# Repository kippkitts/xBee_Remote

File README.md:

xBee_Remote
===========

The XBee Remote is a fully programmable remote control that can be used to operate robots or other systems that are equipped with an XBee transceiver.  It features two thumb joysticks, five pushbutton switches, and an LCD display, the functions of which can be programmed into the onboard Atmega32u4 microcontroller.  This repository contains the Eagle files for the remote.

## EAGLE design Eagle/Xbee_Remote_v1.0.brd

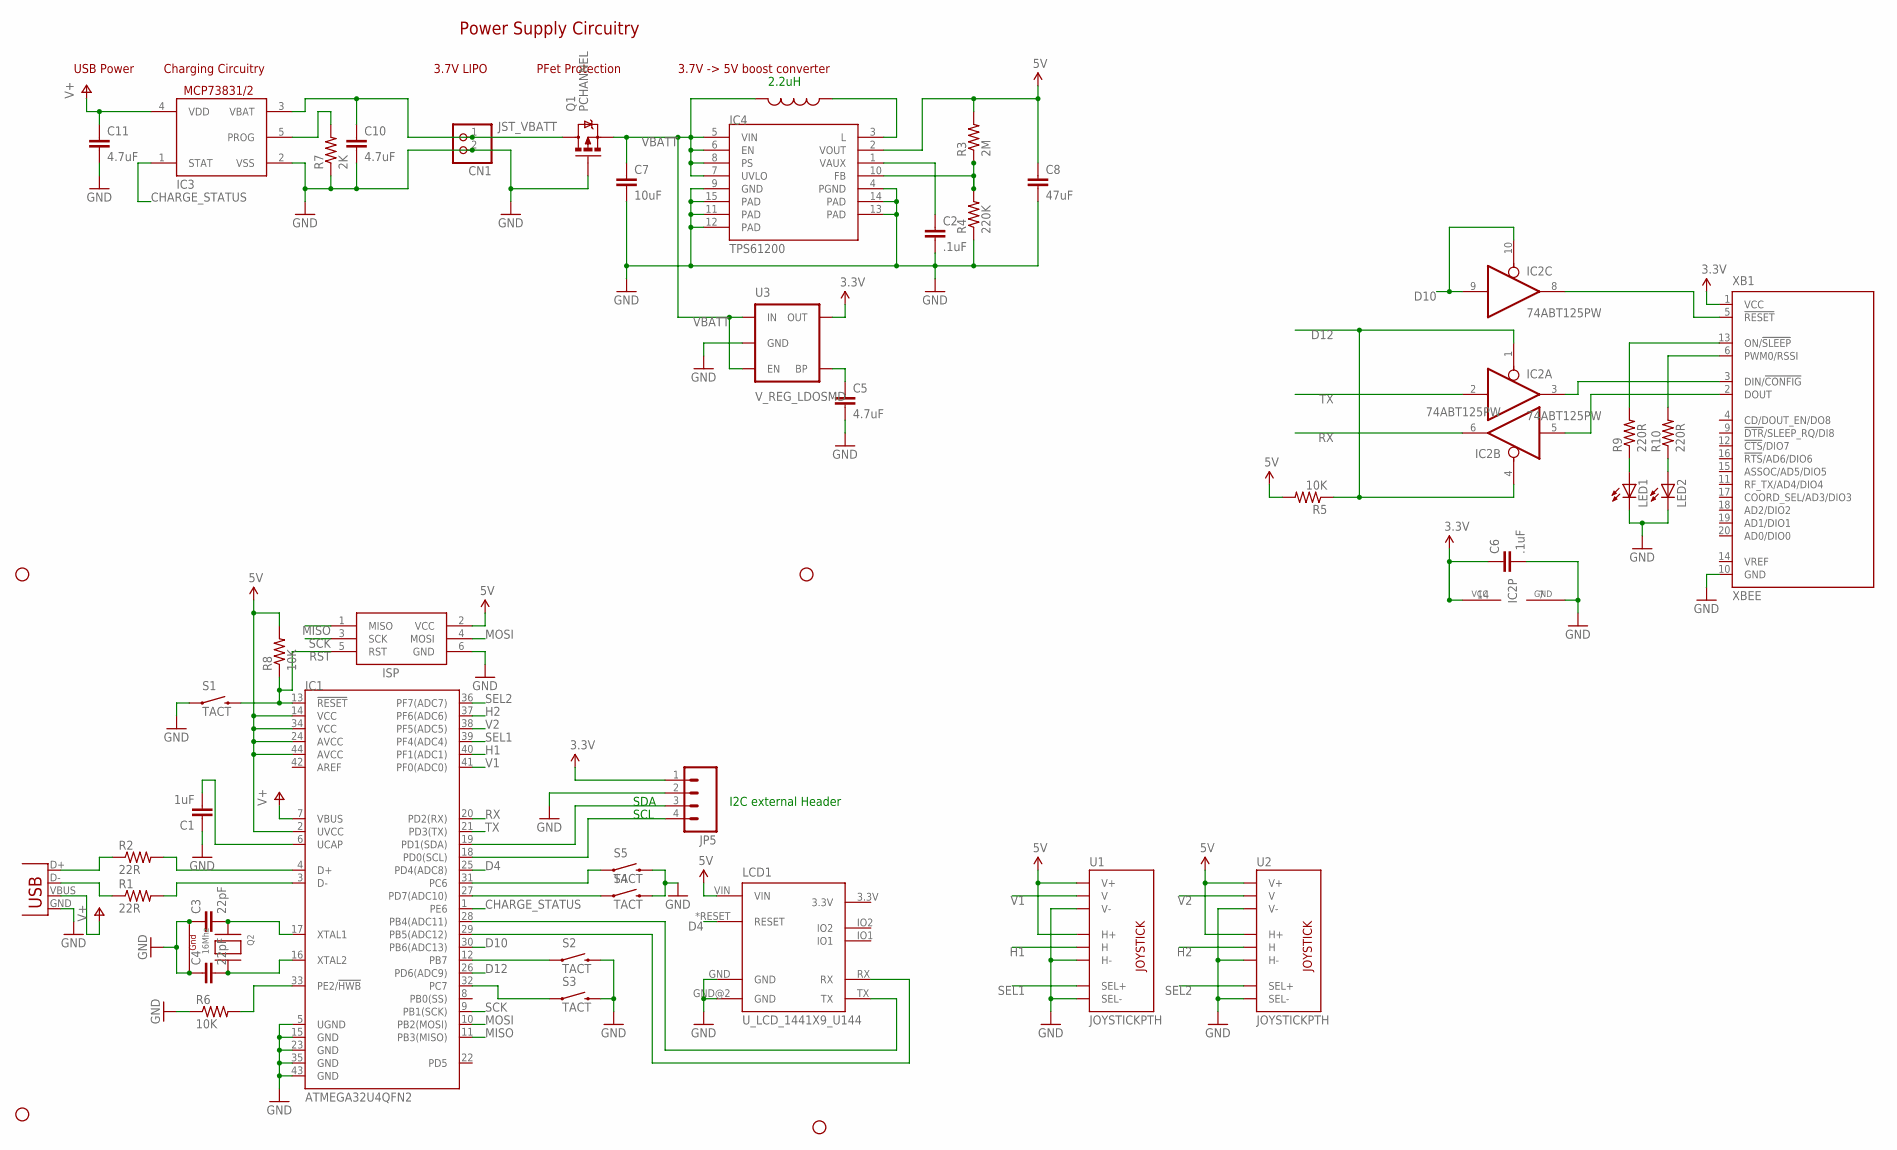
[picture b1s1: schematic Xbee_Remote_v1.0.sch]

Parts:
C1: 1uF; 0805
C2, C6: .1uF; 0805
C3, C4: 22pF; 0805
C5, C10, C11: 4.7uF; 0805
C7: 10uF; 0805
C8: 47uF; 1206
CN1: JST_2PIN-SMT-RA; JST-PH-2-SMT-RA
IC1: ATMEGA32U4QFN2; QFN-44-NOPAD
IC2: 74ABT125PW; TSSOP14
IC3: MCP73831/OT; SOT23-5L
IC4: TPS61200; QFN-10_PAD
ISP: AVRISP-6; AVRISP
JP1, JP2, JP3, JP4: STAND-OFF
JP5: M04PTH; 1X04
L1: 2.2uH; COILCRAFT_EPL2014
LCD1: U_LCD_1441X9_U144; U_LCD_144
LED1, LED2: LEDCHIPLED_0805; CHIPLED_0805
Q1: PCHANNEL; SOT23-3
Q2: 16Mhz; NX3225
R1, R2: 22R; 0805
R3: 2M; 0805
R4: 220K; 0805
R5, R6, R8: 10K; 0805
R7: 2K; 0805
R9, R10: 220R; 0805
S1, S2, S3, S4, S5: TACT; TACTILE_SWITCH_SMD
U1, U2: JOYSTICKPTH; JOYSTICK
U3: V_REG_LDOSMD; SOT23-5
X1: USB-MICROB
XB1: XBEE

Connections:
3.3V: C6.1, IC2.14 (VCC), JP5.1, U3.5 (OUT), XB1.1 (VCC)
5V: C8.1, IC1.2 (UVCC), IC1.14 (VCC), IC1.24 (AVCC), IC1.34 (VCC), IC1.44 (AVCC), IC4.2 (VOUT), ISP.2 (VCC), LCD1.VIN, R3.2, R5.2, R8.2, U1.H1 (H+), U1.V1 (V+), U2.H1 (H+), U2.V1 (V+)
CHARGE_STATUS: IC1.1 (PE6), IC3.1 (STAT)
D2: IC1.19 (PD1(SDA)), JP5.3
D3: IC1.18 (PD0(SCL)), JP5.4
D4: IC1.25 (PD4(ADC8)), LCD1.*RESET (RESET)
D5: IC1.31 (PC6), S5.1
D6: IC1.27 (PD7(ADC10)), S4.1
D10: IC1.30 (PB6(ADC13)), IC2.9 (I), IC2.10 (OE)
D11: IC1.12 (PB7), S2.1
D12: IC1.26 (PD6(ADC9)), IC2.1 (OE), IC2.4 (OE), R5.1
D13: IC1.32 (PC7), S3.1
GND: C1.1, C2.2, C3.1, C4.1, C5.2, C6.2, C7.2, C8.2, C10.2, C11.2, CN1.2 (1), IC1.5 (UGND), IC1.15 (GND), IC1.23 (GND), IC1.35 (GND), IC1.43 (GND), IC2.7 (GND), IC3.2 (VSS), IC4.4 (PGND), IC4.9 (GND), IC4.11 (PAD), IC4.12 (PAD), IC4.13 (PAD), IC4.14 (PAD), IC4.15 (PAD), ISP.6 (GND), JP5.2, LCD1.GND, LCD1.GND@2 (GND), LED1.C, LED2.C, Q1.1 (G), Q2.2 (G1), Q2.4 (G2), R4.1, R6.1, R7.1, S1.1, S2.3 (2), S3.3 (2), S4.3 (2), S5.3 (2), U1.B2A (SEL-), U1.H3 (H-), U1.V3 (V-), U2.B2A (SEL-), U2.H3 (H-), U2.V3 (V-), U3.2 (GND), X1.GND, XB1.10 (GND)
H1: IC1.40 (PF1(ADC1)), U1.H2 (H)
H2: IC1.37 (PF6(ADC6)), U2.H2 (H)
JST_VBATT: C10.1, CN1.1 (2), IC3.3 (VBAT), Q1.3 (D)
LCD_RX: IC1.29 (PB5(ADC12)), LCD1.RX
LCD_TX: IC1.28 (PB4(ADC11)), LCD1.TX
MISO: IC1.11 (PB3(MISO)), ISP.1 (MISO)
MOSI: IC1.10 (PB2(MOSI)), ISP.4 (MOSI)
unnamed: R2.1, X1.D+
unnamed: R1.1, X1.D-
unnamed: IC1.4 (D+), R2.2
unnamed: IC1.3 (D-), R1.2
unnamed: C1.2, IC1.6 (UCAP)
unnamed: IC3.5 (PROG), R7.2
unnamed: IC4.3 (L), L1.P$1 (1)
unnamed: C5.1, U3.4 (BP)
unnamed: IC4.10 (FB), R3.1, R4.2
unnamed: C2.1, IC4.1 (VAUX)
unnamed: C3.2, IC1.17 (XTAL1), Q2.1 (X1)
unnamed: C4.2, IC1.16 (XTAL2), Q2.3 (X2)
unnamed: IC2.8 (O), XB1.5 (!RESET)
unnamed: IC1.33 (PE2/!HWB), R6.2
unnamed: LED1.A, R9.1
unnamed: LED2.A, R10.1
ON: R9.2, XB1.13 (ON/!SLEEP)
RSSI: R10.2, XB1.6 (PWM0/RSSI)
RST: IC1.13 (!RESET), ISP.5 (RST), R8.1, S1.3 (2)
RX: IC1.20 (PD2(RX)), IC2.6 (O)
SCK: IC1.9 (PB1(SCK)), ISP.3 (SCK)
SEL1: IC1.39 (PF4(ADC4)), U1.B1A (SEL+)
SEL2: IC1.36 (PF7(ADC7)), U2.B1A (SEL+)
TX: IC1.21 (PD3(TX)), IC2.2 (I)
V1: IC1.41 (PF0(ADC0)), U1.V2 (V)
V2: IC1.38 (PF5(ADC5)), U2.V2 (V)
V+: C11.1, IC1.7 (VBUS), IC3.4 (VDD), X1.VBUS
VBATT: C7.1, IC4.5 (VIN), IC4.6 (EN), IC4.7 (UVLO), IC4.8 (PS), L1.P$2 (2), Q1.2 (S), U3.1 (IN), U3.3 (EN)
XBEE_RX: IC2.3 (O), XB1.3 (DIN/!CONFIG)
XBEE_TX: IC2.5 (I), XB1.2 (DOUT)

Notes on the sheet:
3.7V LIPO
PFet Protection
3.7V -> 5V boost converter
Power Supply Circuitry
USB Power
Charging Circuitry
2.2uH
I2C external Header
SDA
SCL

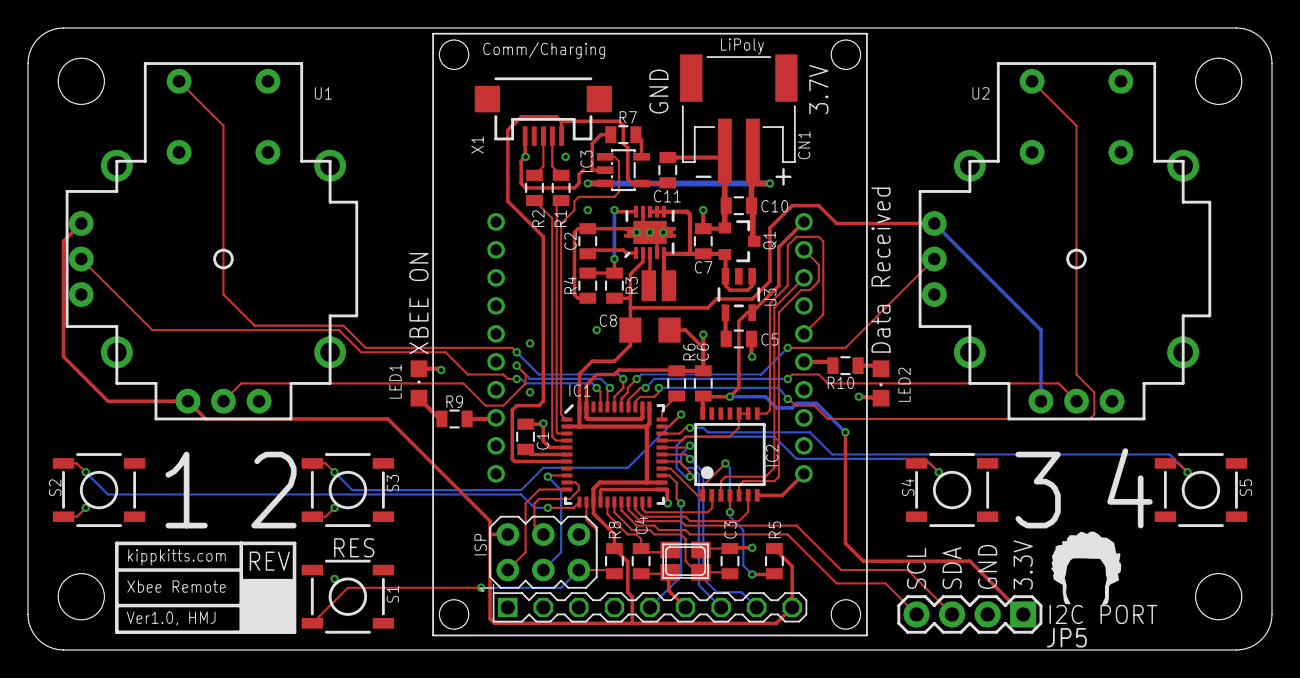
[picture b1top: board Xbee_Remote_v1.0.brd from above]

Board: 2 copper layers, 88.9 x 44.5 mm, 48 parts (1 on the bottom side), 50 nets.

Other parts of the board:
U$9: TOP_DOCU_5MM

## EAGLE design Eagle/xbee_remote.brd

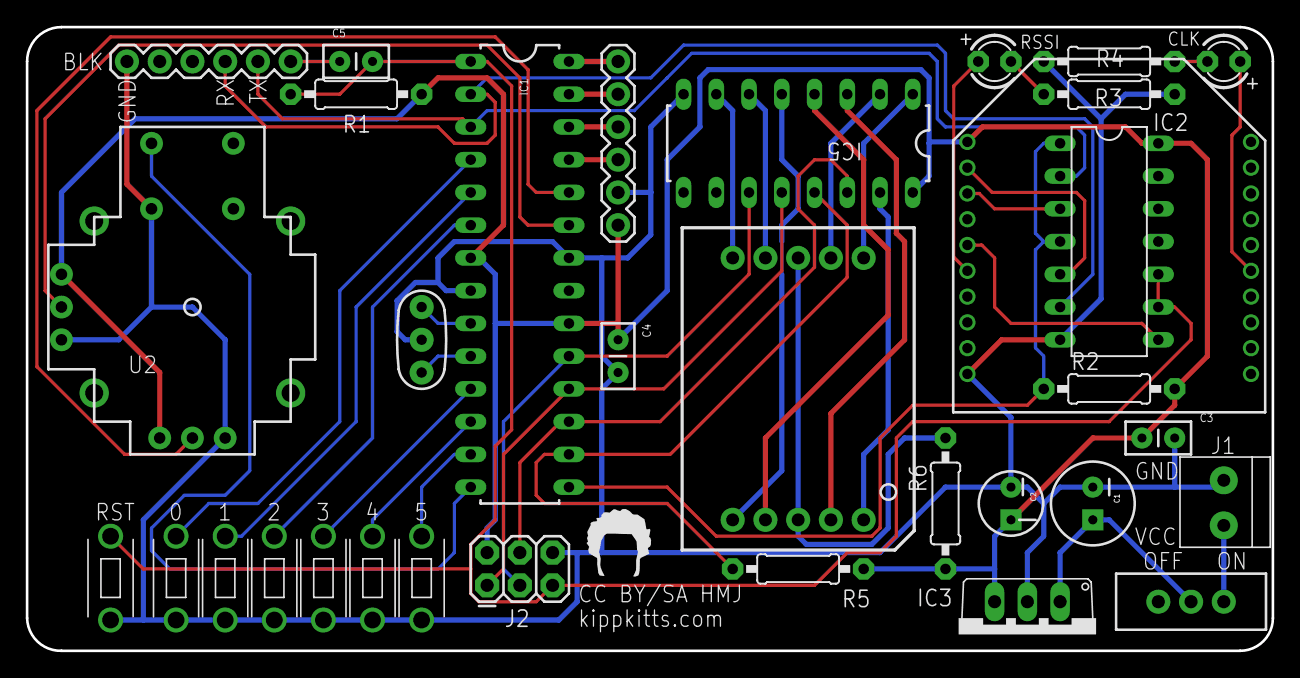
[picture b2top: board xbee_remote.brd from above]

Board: 2 copper layers, 96.6 x 48.4 mm, 34 parts (0 on the bottom side), 44 nets.

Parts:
C1: 100uF; CPOL-RADIAL-100UF-25V
C2: 10uF; CPOL-RADIAL-10UF-25V
C3, C4, C5: .1uF; CAP-PTH-SMALL2
CLK: LED3MM
IC1: AVR-MEGA8-PPTH; DIL28-3
IC2: 74LS125N; DIL14
IC3: UA78M33CKCS; TO220V
IC5: 74LS595N; DIL16
J1: 1X2-3.5MM; 3.5MMTERM
J2: AVR ICSP; 2X3
JP1, JP3: 1X06
R1, R2, R5: 10K; 0207/10
R3, R4: 150; 0207/10
R6: 1K; 0207/10
RSSI: LED3MM
S1: SWITCH-SPDT
U2: JOYSTICKPTH; JOYSTICK
U$2: TOP_DOCU_5MM
U$4: 7-SEGMENT-DISPLAY-1"-RED; 7-SEGMENT-1"PTH
U$8, U$9, U$10, U$11, U$12, U$13, U$14: TACT_TL1107
XB1: XBEE
Y1: RESONATORPTH; RESONATOR-PTH

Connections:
1: IC5.5, U$4.1
2: IC5.4, U$4.2
3.3V: C2.1, C3.1, C4.1, IC1.7, IC1.20, IC2.14, IC3.3, IC5.16, J2.2, JP3.1, R1.2, R2.2, R5.2, R6.1, U2.H1, U2.V1, XB1.1
3V3_/RST: IC2.8, XB1.5
3V3_RX: IC2.5, XB1.2
3V3_TX: IC2.3, XB1.3
4: IC5.3, U$4.4
5: IC5.15, U$4.5
6: IC5.1, U$4.6
7: IC5.2, U$4.7
7_SEG_ENABLE: IC1.16, IC5.13, R5.1
9: IC5.6, U$4.9
10: IC5.7, U$4.10
/RES: C5.2, IC1.1, IC2.9, IC2.10, J2.5, R1.1, U$8.1
/XBEE_EN: IC1.15, IC2.1, IC2.4, R2.1
A2: IC1.25, JP3.3
A3: IC1.26, JP3.4
DS: IC1.17, IC5.14, J2.4
GND: C1.2, C2.2, C3.2, C4.2, IC1.8, IC1.22, IC2.7, IC3.2, IC5.8, J1.1, J2.6, JP1.6, JP3.2, R3.1, R4.1, U2.B2A, U2.H3, U2.V3, U$8.2, U$9.2, U$10.2, U$11.2, U$12.2, U$13.2, U$14.2, XB1.10, Y1.2
IO0: IC1.4, U$9.1
IO1: IC1.5, U$10.1
IO2: IC1.6, U$11.1
IO3: IC1.11, U$12.1
IO4: IC1.12, U$13.1
IO5: IC1.13, U$14.1
IO_SEL: IC1.14, U2.B1A
unnamed: IC1.9, Y1.1
unnamed: IC1.10, Y1.3
unnamed: J1.2, S1.1
unnamed: C5.1, JP1.1
unnamed: R6.2, U$4.3, U$4.8
unnamed: RSSI.A, XB1.6
unnamed: R3.2, RSSI.K
unnamed: CLK.A, XB1.15
unnamed: CLK.K, R4.2
RX: IC1.2, IC2.6, JP1.3
SCL: IC1.28, JP3.6
SDA: IC1.27, JP3.5
SH_CP: IC1.19, IC5.11, J2.3
ST_CP: IC1.18, IC5.12, J2.1
TX: IC1.3, IC2.2, JP1.2
VIN: C1.1, IC3.1, S1.2
VIN_H: IC1.24, U2.H2
VIN_V: IC1.23, U2.V2

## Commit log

2014-03-26 Create Repository
2014-04-22 Replace Eagle Files

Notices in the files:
Eagle/xbee_remote.brd:
CC BY/SA HMJ
parts and their libraries:
SparkFun: Licensing: CC v3.0 Share-Alike You are welcome to use this library for commercial purposes.
